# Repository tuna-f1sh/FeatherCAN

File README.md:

# Board Details

* MCP2515 SPI CAN Controller: Provides the missing CAN peripheral for the Feather SAMD21. Compatible with the [MCP2515 Arduino Library](https://github.com/autowp/arduino-mcp2515) initialising with `CS #6` and `INT #5`. The track to `#5` can be cut if the user does not require interrupts and wishes to use the pin for something else. 16 MHz crystal used for high-data rate capture.
* SN65HVD230 CAN Transceiver: Front-end for the differential CAN signals; -2/7 V common mode range on bus, +/- 25 kV ESD protection and upto 1 Mbps datarate. Slope can be controlled with the R<sub>s</sub> resistor `R2`, by default it is configured in 'high-speed' mode (RX and TX active). A 120R termination resistor is on-board but not connected by default (a solder link is provided to being in circuit). UPDATE: I've now routed the transeiver RX/TX to pins `#9` and `#10` so that the _STM32 Feather_ can use the on-board CAN peripheral rather than MCP2515.
* RX/TX LEDS: I've tied pull-up LEDs on the transmission lines between the MCP2515 and MCP2551 to provide indication of activity. They should not degrade the signal as they are low current (2 mA) but can be removed if edges are lost at high-speed.
* MCP1703T-5002E: 5 V LDO provides power to the Feather via __VUSB__ given a source of 5-16 V. The board __3V3__ is then powered by the Feather's on-board 3V3 regulator. __NOTE__ VIN should not be supplied with __VUSB__ to avoid back-powering the USB port.
* DS3231: Commonly used high-accuracy RTC module with on-board CR1220 back-up battery. Compatible with the [DS3231 Arduino Library](https://github.com/JChristensen/DS3232RTC).
* Hand-drawn silk art! Something I did on the train, inspired by feather's and bikes! CAN is synonymous with the automotive industry so I wanted to put a bike spin on things...

## Potential Improvements for Mass Assembly

* Make 0603 passives 0402.
* Use same CR1220 holder as Adafruit RTC Wing.

# Availability

I have some bare boards in fabrication at the moment, which I plan to hand-assemble for my own use. If there is interest, I will get an assembly run done (unless it wins the competition of course!) after this validation.

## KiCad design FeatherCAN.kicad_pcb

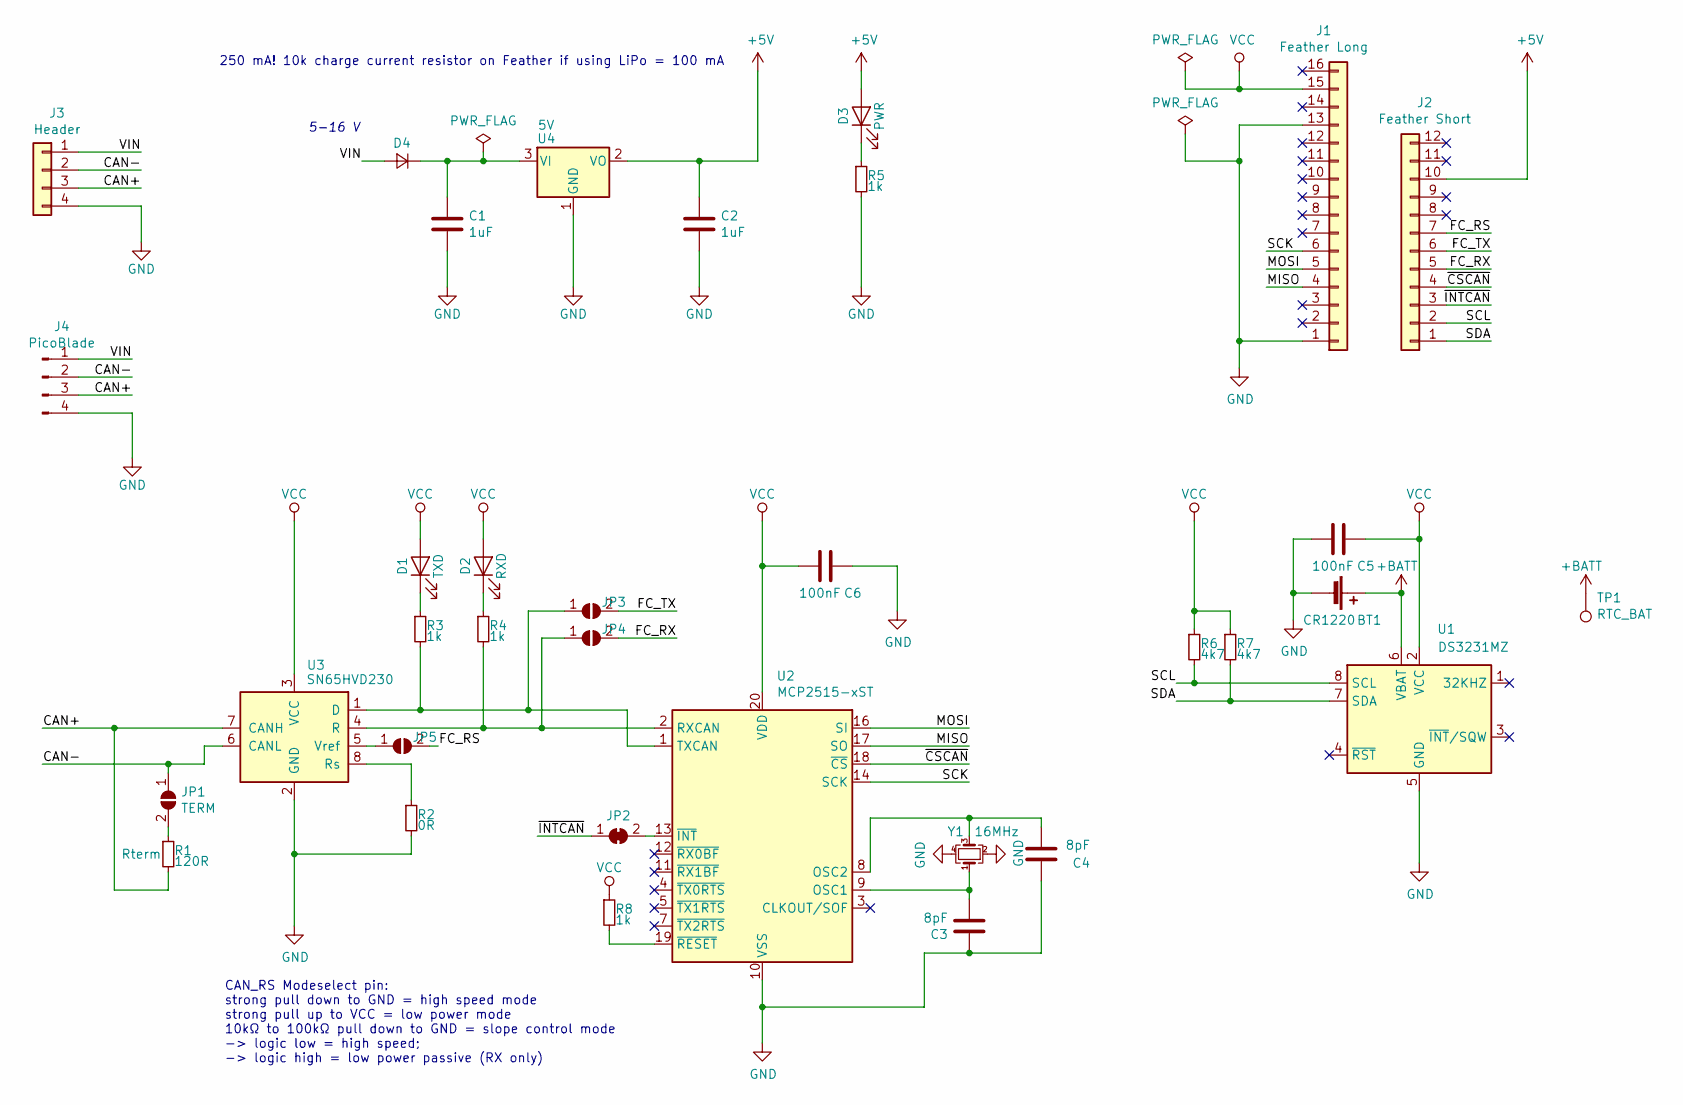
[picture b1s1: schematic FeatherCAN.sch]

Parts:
BT1: CR1220; BatteryHolder_LINX_BAT-HLD-012-SMT; MPN BAT-HLD-012-SMT-TR
C1, C2: 1uF; C_0603_1608Metric
C3, C4: 8pF; C_0603_1608Metric
C5, C6: 100nF; C_0603_1608Metric
D1: TXD; LED_0603_1608Metric; MPN APT1608LSECK/J4-PRV
D2: RXD; LED_0603_1608Metric; MPN APT1608LSECK/J4-PRV
D3: PWR; LED_0603_1608Metric; MPN APT1608LZGCK
D4: 40V 200mA; D_0603_1608Metric; MPN SD0603S040S0R2
J1: Feather Long; PinHeader_1x16_P2.54mm_Vertical
J2: Feather Short; PinHeader_1x12_P2.54mm_Vertical
J3: Header; PinHeader_1x04_P2.54mm_Vertical
J4: PicoBlade; Molex_PicoBlade_53261-0471_1x04-1MP_P1.25mm_Horizontal; MPN 53261-0471
JP1: TERM; SolderJumper-2_P1.3mm_Open_RoundedPad1.0x1.5mm
JP2: INT; SolderJumper-2_P1.3mm_Bridged_RoundedPad1.0x1.5mm
JP3, JP4, JP5: INT; SolderJumper-2_P1.3mm_Open_RoundedPad1.0x1.5mm
R1: 120R; R_0603_1608Metric
R2: 0R; R_0603_1608Metric
R3, R4, R5, R8: 1k; R_0603_1608Metric
R6, R7: 4k7; R_0603_1608Metric
TP1: RTC_BAT; TestPoint_Pad_D2.5mm
U1: DS3231MZ; SOIC-8_3.9x4.9mm_P1.27mm; MPN DS3231MZ+
U2: MCP2515-xST; TSSOP-20_4.4x6.5mm_P0.65mm; MPN MCP2515T-I/ST
U3: SN65HVD230; SOIC-8_3.9x4.9mm_P1.27mm; MPN SN65HVD230DR
U4: 5V; SOT-23; MPN MCP1703T-5002E/CB
Y1: 16MHz; Crystal_SMD_3225-4Pin_3.2x2.5mm; MPN TSX-3225 16.0000MF18X-AC0

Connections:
+5V: C2.1, D3.2 (A), J2.10, U4.2 (VO)
+BATT: BT1.1 (+), TP1.1, U1.6 (VBAT)
/CAN+: J3.3, J4.3, R1.2, U3.7 (CANH)
/CAN-: J3.2, J4.2, JP1.1 (A), U3.6 (CANL)
/FC_RS: J2.7, JP5.2 (B)
/FC_RX: J2.5, JP4.2 (B)
/FC_TX: J2.6, JP3.2 (B)
/MISO: J1.4, U2.17 (SO)
/MOSI: J1.5, U2.16 (SI)
/SCK: J1.6, U2.14 (SCK)
/SCL: J2.2, R6.2, U1.8 (SCL)
/SDA: J2.1, R7.2, U1.7 (SDA)
/VIN: D4.2 (A), J3.1, J4.1
/~CSCAN: J2.4, U2.18 (~CS)
/~INTCAN: J2.3, JP2.1 (A)
GND: BT1.2 (-), C1.2, C2.2, C3.1, C4.1, C5.2, C6.1, J1.1, J1.13, J3.4, J4.4, R2.2, R5.2, U1.5 (GND), U2.10 (VSS), U3.2 (GND), U4.1 (GND), Y1.2, Y1.4
unnamed: C1.1, D4.1 (K), U4.3 (VI)
unnamed: C3.2, U2.9 (OSC1), Y1.1
unnamed: C4.2, U2.8 (OSC2), Y1.3
unnamed: D1.1 (K), R3.1
unnamed: D2.1 (K), R4.1
unnamed: D3.1 (K), R5.1
unnamed: JP1.2 (B), R1.1
unnamed: JP2.2 (B), U2.13 (~INT)
unnamed: JP3.1 (A), R3.2, U2.1 (TXCAN), U3.1 (D)
unnamed: JP4.1 (A), R4.2, U2.2 (RXCAN), U3.4 (R)
unnamed: JP5.1 (A), U3.5 (Vref)
unnamed: R2.1, U3.8 (Rs)
unnamed: R8.2, U2.19 (~RESET)
VCC: C5.1, C6.2, D1.2 (A), D2.2 (A), J1.15, R6.1, R7.1, R8.1, U1.2 (VCC), U2.20 (VDD), U3.3 (VCC)

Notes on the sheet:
5-16 V
250 mA! 10k charge current resistor on Feather if using LiPo = 100 mA
CAN_RS Modeselect pin: strong pull down to GND = high speed mode strong pull up to VCC = low power mode 10kΩ to 100kΩ pull down to GND = slope control mode -> logic low = high speed; -> logic high = low power passive (RX only)

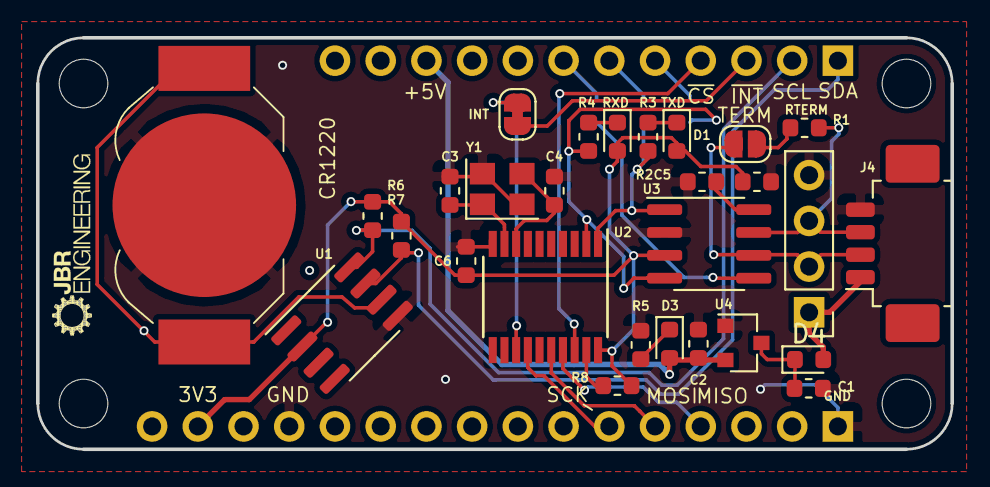
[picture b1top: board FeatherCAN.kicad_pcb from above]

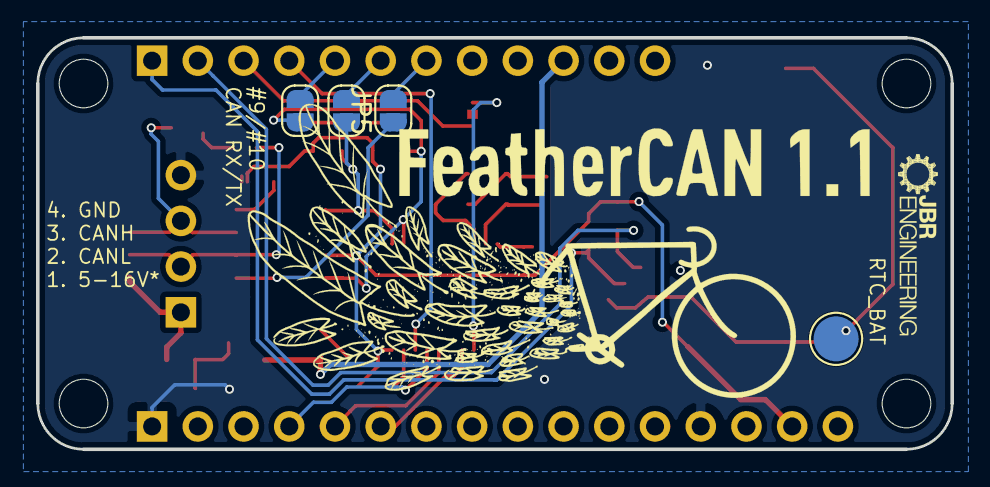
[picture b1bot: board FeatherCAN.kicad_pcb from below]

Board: 2 copper layers, 50.8 x 22.9 mm, 34 parts (6 on the bottom side), 30 nets.

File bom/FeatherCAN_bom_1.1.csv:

Component,Description,Part,References,Value,Footprint,Quantity Per PCB,Datasheet,SKU,Vendor,MPN,MFN,Characteristics,Notes,Config
1,Single-cell battery,Battery_Cell,BT1,CR1220,BatteryHolder_LINX_BAT-HLD-012-SMT,1,~,BAT-HLD-012-SMTCT-ND,Digikey,BAT-HLD-012-SMT-TR,Linx Technologies,,,
2,Unpolarized capacitor,C,C5 C6,100nF,C_0603_1608Metric,2,~,,,,,X7R 6V,,
3,Unpolarized capacitor,C,C1 C2,1uF,C_0603_1608Metric,2,~,,,,,X5R 20V,,
4,Unpolarized capacitor,C,C3 C4,8pF,C_0603_1608Metric,2,~,,,,,NPO 6V,,
5,"Diode, small symbol",D_Small,D4,40V 200mA,D_0603_1608Metric,1,~,478-7798-1-ND,Digikey,SD0603S040S0R2,AVX Corporation,40V 200mA,Don't allow back powering bus and reverse polarity protect,
6,Light emitting diode,LED,D3,PWR,LED_0603_1608Metric,1,http://www.kingbrightusa.com/images/catalog/SPEC/APT1608LZGCK.pdf,754-1934-1-ND,Digikey,APT1608LZGCK,Kingbright,Green,,
7,Light emitting diode,LED,D2,RXD,LED_0603_1608Metric,1,http://www.kingbrightusa.com/images/catalog/SPEC/APT1608LSEC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,754-1931-1-ND,Digikey,APT1608LSECK/J4-PRV,Kingbright,Orange,,
8,Light emitting diode,LED,D1,TXD,LED_0603_1608Metric,1,http://www.kingbrightusa.com/images/catalog/SPEC/APT1608LSEC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,754-1931-1-ND,Digikey,APT1608LSECK/J4-PRV,Kingbright,Orange,,
9,"Generic connector, single row, 01x04, script generated (kicad-library-utils/schlib/autogen/connector/)",Conn_01x04_Male,J4,PicoBlade,Molex_PicoBlade_53261-0471_1x04-1MP_P1.25mm_Horizontal,1,~,WM7622CT-ND,Digikey,53261-0471,Molex,,,
10,"Resistor, small symbol",R_Small,R2,0R,R_0603_1608Metric,1,,,,,,,"Rext controls mode and slew rate. GND = high-speed, 10 μA < -IRS < 200 μA slope control",
11,"Resistor, small symbol",R_Small,R1,120R,R_0603_1608Metric,1,,,,,,1%,,
12,"Resistor, small symbol",R_Small,R3 R4 R5 R8,1k,R_0603_1608Metric,4,,,,,,,,
13,"Resistor, small symbol",R_Small,R6 R7,4k7,R_0603_1608Metric,2,,,,,,,,
14,"250mA Low Quiscent Current LDO, 5.0V output, SOT-23",MCP1700-5002E_SOT23,U4,5V,SOT-23,1,http://www.microchip.com/mymicrochip/filehandler.aspx?ddocna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,MCP1703T-5002E/CBCT-ND,Digikey,MCP1703T-5002E/CB,Microchip Technology,,,
15,"±5ppm, I2C Real-Time Clock SOIC-8",DS3231MZ,U1,DS3231MZ,SOIC-8_3.9x4.9mm_P1.27mm,1,http://datasheets.maximintegrated.com/en/ds/DS3231M.pdf,DS3231MZ+-ND,Digikey,DS3231MZ+,Maxim,,,
16,"Stand-Alone CAN Controller with SPI Interface, TSSOP-20",MCP2515-xST,U2,MCP2515-xST,TSSOP-20_4.4x6.5mm_P0.65mm,1,http://ww1.microchip.com/downloads/en/DeviceDoc/MCP2515-Stan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,MCP2515T-I/STCT-ND,Digikey,MCP2515T-I/ST,Microchip Technology,,,
17,"CAN Bus Transceivers, 3.3V, 1Mbps, Low-Power capabilities, SOIC",SN65HVD230,U3,SN65HVD230,SOIC-8_3.9x4.9mm_P1.27mm,1,http://www.ti.com/lit/ds/symlink/sn65hvd230.pdf,296-11654-1-ND,Digikey,SN65HVD230DR,Texas Instruments,,MCP2551 drop in replacement,
18,"Four pin crystal, GND on pins 2 and 4, small symbol",Crystal_GND24_Small,Y1,16MHz,Crystal_SMD_3225-4Pin_3.2x2.5mm,1,https://support.epson.biz/td/api/doc_check.php?dl=brief_TSX-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,SER4070CT-ND,Digikey,TSX-3225 16.0000MF18X-AC0,Epson,,,





Component Groups:,23
Component Count:,32
Fitted Components:,25
Number of PCBs:,1
Total components:,25
Schematic Version:,1.1
Schematic Date:,2020-01-22
PCB Variant:,[u'default']
BoM Date:,"2020 February 04, Tuesday 14:12:21"
Schematic Source:,/Users/john/Dropbox/specialized/FeatherCAN/FeatherCAN.sch
KiCad Version:,Eeschema (5.1.5-0-10_14)

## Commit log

2019-12-23 initial schematic capture and layout complete
2019-12-23 first version sent for production review
2019-12-28 add README and silk logo
2019-12-28 reverse polority protect and clamp VIN
2020-01-06 add part numbers
2020-01-15 pull-up on MCP reset and fix 4-pad crystal pins
2020-01-22 add CAN transeiver lines for STM32 Feather peripheral
    STM32 Feather has CAN RX/TX on #9 and #10. Can be cut if user wants to
    use pins on other Feather.
2020-01-22 MCP2515 Vdd is +5 V
2020-02-04 gerbers and kitspcae
2020-02-04 correct MFP/MPN and add kitspace tsv
2020-02-04 Create LICENSE
2020-02-04 MCP2551 swap to SN65 for Vcc logic
